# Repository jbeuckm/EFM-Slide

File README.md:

# EFM-Slide
EFM Slide circuit layout for eurorack

Schematic from page 9 here: http://electro-music.com/forum/phpbb-files/wildcat_001_390.pdf

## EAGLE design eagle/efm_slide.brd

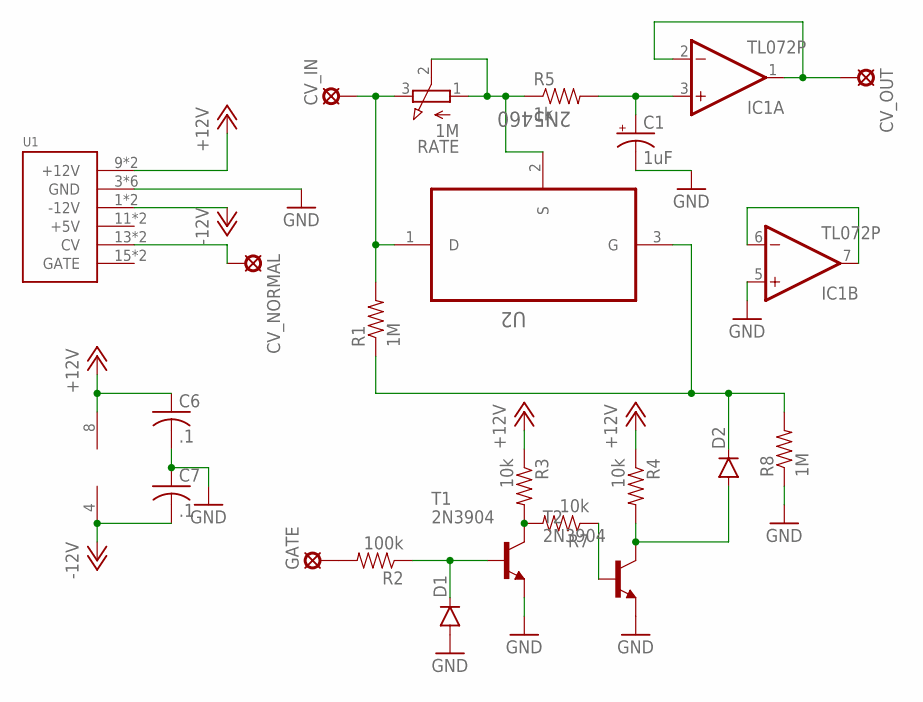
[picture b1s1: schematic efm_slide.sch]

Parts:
C1: 1uF; B45181A
C6, C7: .1; C025-024X044
CV_IN: LSP10
CV_NORMAL: LSP10
CV_OUT: LSP10
D1, D2: DIODEKIT; DIODE-1N4148-KIT
GATE: LSP10
IC1: TL072P; DIL08
R1, R8: 1M; AXIAL-0.4
R2: 100k; AXIAL-0.4
R3, R4, R7: 10k; AXIAL-0.4
R5: 1k; AXIAL-0.4
RATE: 1M; 3RP/1610N
T1, T2: 2N3904; TO92
U1: POWER; POWER_16
U2: 2N5460; TO127P254X732-3

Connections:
+12V: C6.1, IC1.8 (V+), R3.P$1 (1), R4.P$1 (1), U1.9 (+12V), U1.10 (+12V)
-12V: C7.2, IC1.4 (V-), U1.1 (-12V), U1.2 (-12V)
GND: C1.-, C6.2, C7.1, D1.A, IC1.5 (+IN), R8.P$1 (1), T1.3 (E), T2.3 (E), U1.3 (GND), U1.4 (GND), U1.5 (GND), U1.6 (GND), U1.7 (GND), U1.8 (GND)
unnamed: CV_NORMAL.MP, U1.13 (CV), U1.14 (CV)
unnamed: CV_IN.MP, R1.P$2 (2), RATE.3 (E), U2.1 (D)
unnamed: R5.P$1 (1), RATE.1 (A), RATE.2 (S), U2.2 (S)
unnamed: C1.+, IC1.3 (+IN), R5.P$2 (2)
unnamed: D2.C, R1.P$1 (1), R8.P$2 (2), U2.3 (G)
unnamed: CV_OUT.MP, IC1.1 (OUT), IC1.2 (-IN)
unnamed: D1.C, R2.P$1 (1), T1.2 (B)
unnamed: GATE.MP, R2.P$2 (2)
unnamed: R3.P$2 (2), R7.P$2 (2), T1.1 (C)
unnamed: R7.P$1 (1), T2.2 (B)
unnamed: IC1.6 (-IN), IC1.7 (OUT)
unnamed: D2.A, R4.P$2 (2), T2.1 (C)

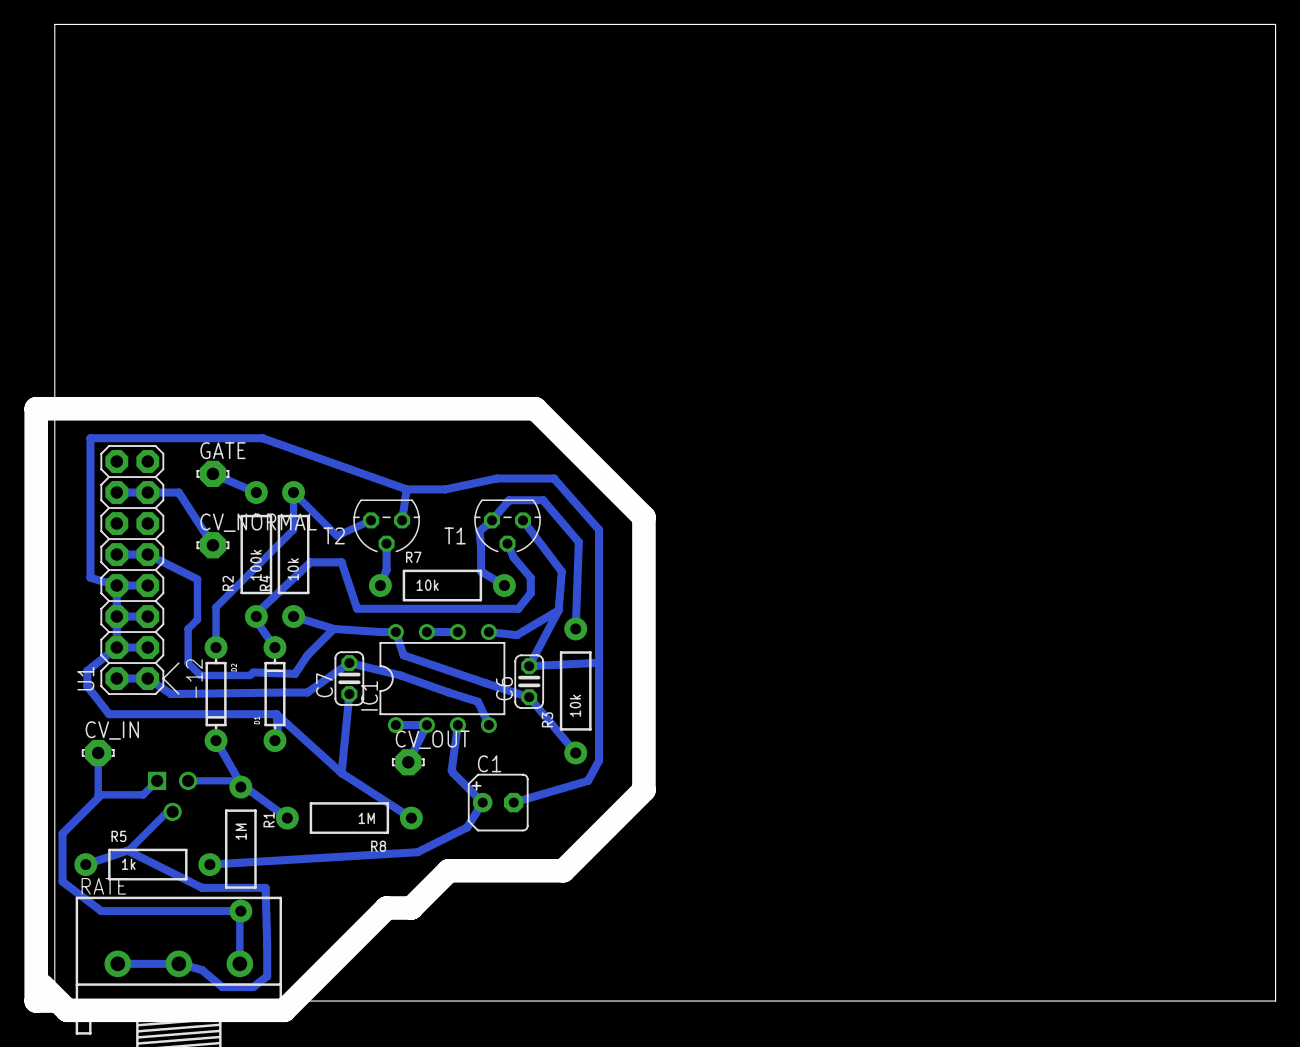
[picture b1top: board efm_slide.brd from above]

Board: 2 copper layers, 100.6 x 79.8 mm, 22 parts (1 on the bottom side), 15 nets.

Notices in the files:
parts and their libraries:
SparkFun-DiscreteSemi: Licensing: Creative Commons ShareAlike 4.0 International - https://creativecommons.org/licenses/by-sa/4.0
